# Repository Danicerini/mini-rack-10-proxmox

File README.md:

# Mini rack 10" per cluster Proxmox

Armadio da 10 pollici stampato in 3D per **tre mini PC** (un cluster Proxmox), uno **switch di rete** e una **plancia di controllo** con display. Si monta tutto con viti normali, senza colla e senza inserti a caldo.

|  |  |
|---|---|

## Cosa c'è
- **4 vani**:
  - 1 vano alto 51 mm in basso per un Teclast N30;
  - 2 vani da 1U per due HP EliteDesk Mini (G2 e G5);
  - 1 vano da 2U in alto con switch, ESP32 e plancia inclinata.
- **Frontali con display OLED** per ogni PC: nome, temperatura, CPU, RAM e da quanto è acceso. Il vetro del display arriva a filo del frontale.
- **Plancia di controllo inclinata**:
  - display TFT da 2,4" con 5 pagine (panoramica, nodi, macchine, backup e rete, impostazioni);
  - barra a 10 LED con la CPU media del cluster (lampeggia tutta se il cluster perde il quorum);
  - joystick a 4 direzioni: cambia pagina, apre nodi e macchine e, **tenendo premuto 1,5 s**, accende (Wake-on-LAN), riavvia o spegne i nodi e accende, riavvia, spegne o ferma VM e container;
  - impostazioni dal joystick (luminosità, spegnimento schermi da 5 secondi a 30 minuti, scorrimento automatico) salvate nella memoria dell'ESP32: restano anche dopo un riavvio;
  - sensore di movimento PIR, che spegne i display quando non c'è nessuno.
  - Il logo Proxmox non è incluso (è un marchio): senza il file `logo_proxmox.h` il firmware scrive "Proxmox" in testo. Puoi crearlo tu dal media kit ufficiale di Proxmox.
- **Pannelli laterali traforati** a esagoni per l'aria, **maniglie** per trasportarlo e **piedini**.
- Misure: **260 × 220 × 293 mm** circa.
- Si stampa tutto su un piatto da **256 × 256 mm** (Bambu Lab A1, P1, X1).

## Struttura della repo
| Cartella | Cosa contiene |
|---|---|
| `stl/` | Tutti i pezzi da stampare. `__x4` nel nome vuol dire che ne servono 4. `00_rack_montato_solo_da_guardare.stl` non va stampato. |
| `stampa_bambu/` | Progetto Bambu Studio (`.3mf`) con i pezzi già disposti sui piatti. |
| `openscad/` | Sorgente parametrico `rack10.scad`: tutte le misure sono in cima al file. |
| `istruzioni/` | Manuale di montaggio in PDF, passo per passo, con la viteria in scala 1:1. |
| `elettronica/firmware/` | Firmware ESP32 della plancia e due sketch di prova per i fili. |
| `elettronica/server/` | Script per Proxmox che manda lo stato del cluster all'ESP32 via USB. |
| `elettronica/pcb/` | Circuito stampato (facoltativo) che sostituisce la basetta e i fili Dupont. |
| `elettronica/Schema_collegamenti.pdf` | Schema di tutti i fili. |
| `script/` | Script Python che rigenerano il manuale e il progetto Bambu. |

## Pezzi da stampare
| N. | Pezzo | Quanti | Colore usato |
|---|---|---|---|
| 01 | Montante | 4 | Nero |
| 03 | Cornice sotto | 1 | Bianco |
| 04 | Cornice sopra | 1 | Bianco |
| 05 | Pannello laterale destro | 1 | Nero |
| 06 | Pannello laterale sinistro | 1 | Nero |
| 09 | Maniglia | 2 | Bianco |
| 10 | Piedino | 4 | Bianco |
| 11 | Ripiano HP | 2 | Nero |
| 12 | Ripiano pve1 (Teclast) | 1 | Nero |
| 13 | Ripiano plancia (switch + ESP32) | 1 | Nero |
| 14 | Frontale pve1 | 1 | Nero |
| 15 | Frontale pve2 | 1 | Nero |
| 16 | Frontale pve3 | 1 | Nero |
| 17 | Plancia inclinata | 1 | Nero |
| 18 | Barra fermo switch | 1 | Nero |

In tutto sono **24 pezzi in PLA**. I numeri 02, 07 e 08 non esistono: sono pezzi di versioni precedenti.

**Impostazioni consigliate**:
- PLA, strati da 0,2 mm, 3 pareti e riempimento al 15-20%;
- nel `.3mf` i pezzi sono già disposti e orientati sui piatti: controlla nell'anteprima se qualcuno ha bisogno di supporti;
- tieni il rack lontano da sole e fonti di calore, perché il PLA si deforma sopra i 55 °C circa.

## Viteria
| Sigla | Vite | Quante | Dove |
|---|---|---|---|
| A | M6 × 35 testa bombata | 20 | frontali e plancia (va bene anche M6 × 40) |
| B | M6 × 25 testa bombata | 8 | alette posteriori dei ripiani |
| C | Autofilettante 4 × 25 testa svasata | 8 | cornici sui montanti |
| D | Autofilettante 4 × 20 testa tonda | 4 | maniglie |
| E | Autofilettante 4 × 12 testa tonda | 4 | piedini |
| F | Autofilettante 3 × 12 testa svasata | 26 | pannelli laterali e barra dello switch |
| G | M2 × 6 testa bombata | 14 | display OLED e sensore PIR |
| H | M2,5 × 8 testa bombata | 4 | joystick |
| I | M2,5 × 4 testa bombata | 4 | display TFT |
| N | Dado M6 | 28 | nelle sedi dei montanti |
| R | Rondella piana M6 | 20 | sotto la testa delle viti A |

**Attrezzi**: cacciavite PH2, brugole da 4, 1,5 e 1,3 mm, chiave da 10 o pinza.

## Componenti
**Computer e rete** (il rack è disegnato su queste misure):
| Cosa | Note | Quanti |
|---|---|---|
| Teclast N30 | 114 × 106 × 43,5 mm | 1 |
| HP EliteDesk 800 G2 / G5 Desktop Mini | 177 × 175 × 34 mm | 2 |
| Switch TP-Link TL-SG608E | 8 porte, 158 × 100 × 25 mm | 1 |
| Cavi di rete corti | Cat 6, da 0,25 a 0,5 m | 4 |
| Cavo USB **per dati** | dall'ESP32 a un nodo Proxmox | 1 |

**Elettronica della plancia**:
| Cosa | Note | Quanti |
|---|---|---|
| ESP32 DevKit con basetta a morsetti | basetta 77 × 63 mm | 1 |
| Display TFT 2,4" ST7789 | 320 × 240, SPI | 1 |
| Display OLED 0,96" SSD1306 | I2C, indirizzo 0x3C | 3 |
| Barra LED a 10 segmenti | con due 74HC595 | 1 |
| Joystick KY-023 | 34 × 26 mm | 1 |
| Sensore di movimento HC-SR501 | con lente | 1 |
| Cavi Dupont femmina-femmina | 20 cm | circa 30 |

Con altri PC o un altro switch basta cambiare le misure in cima a `openscad/rack10.scad` e riesportare gli STL.

## Montaggio
Segui il manuale [`istruzioni/Manuale_montaggio_rack_10pollici.pdf`](istruzioni/Manuale_montaggio_rack_10pollici.pdf): ci sono 15 passi illustrati, la viteria disegnata in scala 1:1 (stampa la pagina al 100%) e i controlli finali.

> **Nota sui display OLED:** nella versione attuale dei frontali (14, 15, 16) l'OLED non va più sulle torrette, come mostrato nel manuale. Ora il circuito entra in un incavo sul retro del frontale e il vetro arriva a filo davanti, come nel TFT. Dietro c'è una scanalatura per le saldature dei pin. Le misure del vetro sono nei parametri `oled_glass*` e `oled2_*` di `rack10.scad`: controllale col calibro sui tuoi display.

## Elettronica e software
1. **Collegamenti**: segui [`elettronica/Schema_collegamenti.pdf`](elettronica/Schema_collegamenti.pdf). In breve:

   | Cosa | GPIO |
   |---|---|
   | TFT | CS 5, RESET 4, DC 16, MOSI 23, SCK 18, LED 25 |
   | OLED | SCL 22 per tutti; SDA: pve1 21, pve2 19, pve3 17 |
   | 74HC595 | DS 13, SH_CP 14, ST_CP 27, OE 15 |
   | PIR | 39 |
   | Joystick | VRx 34, VRy 35, SW 33 (alimentato a 3V3) |

2. **Firmware**: apri `elettronica/firmware/cluster_completo/cluster_completo.ino` con Arduino IDE o arduino-cli.
   - Core: esp32 3.x.
   - Librerie: LovyanGFX, ArduinoJson, Adafruit SSD1306 e Adafruit GFX.
   - Le opzioni sono in cima al file: `USE_PIR`, `USE_JOY`, `BRIGHT_TFT`, `SCREEN_OFF_MS` e così via.
   - I nomi dei nodi mostrati sugli OLED sono in `OLED_NODE`.
   ```
   arduino-cli compile --fqbn esp32:esp32:esp32:FlashFreq=40,FlashMode=dio cluster_completo
   arduino-cli upload  --fqbn esp32:esp32:esp32:FlashFreq=40,FlashMode=dio -p COM3 cluster_completo
   ```
   > **Flash a 40 MHz**: molti ESP32 economici hanno una flash Puya (ID `0x852016`) che a 80 MHz legge bene ma ignora in silenzio le scritture del firmware, e le impostazioni si perdono a ogni riavvio. A 40 MHz funziona. Il firmware ha i comandi seriali `SET_GET`, `SET_TEST <tft> <barra> <secondi>` e `FLASH_TEST` per controllarlo.
3. **Server**: l'ESP32 non usa il Wi-Fi. Riceve i dati via USB da un nodo Proxmox.
   - Copia `elettronica/server/cluster-status.py` in `/usr/local/bin/` sul nodo a cui colleghi l'ESP32.
   - Nelle impostazioni in cima al file metti i nomi e gli IP dei tuoi nodi.
   - Attiva il servizio:
     ```
     cp cluster-status.service /etc/systemd/system/
     chmod +x /usr/local/bin/cluster-status.py
     systemctl enable --now cluster-status
     ```
   - Lo script legge lo stato con `pvesh`, solo in lettura.
   - Lo pubblica anche su `http://IP-DEL-NODO:9101/status.json`.
   - Se l'ESP32 è attaccato a un PC Windows invece che al nodo, c'è `ponte_dati_pc.ps1`.
4. **Caricare il firmware senza staccare niente**: se l'ESP32 è collegato al nodo, puoi caricarlo da lì con esptool.
   ```
   systemctl stop cluster-status
   esptool --port /dev/ttyUSB0 --baud 460800 write-flash 0x10000 cluster_completo.ino.bin
   systemctl start cluster-status
   ```
   Carica solo `cluster_completo.ino.bin` a `0x10000`: così le impostazioni salvate restano. Il file `merged.bin` a `0x0` serve solo la prima volta (ESP32 nuovo), perché riscrive tutta la memoria e cancella le impostazioni.

### PCB (facoltativa)
In `elettronica/pcb/` c'è una scheda da 70 × 47 mm che sostituisce basetta e fili. Ci sono due versioni:
- **THT**, da saldare tutta a mano;
- **SMD**, con chip e resistenze montati in fabbrica.

I file per l'ordine (gerber, BOM e CPL per JLCPCB) sono in `elettronica/pcb/produzione/`. I file KiCad sono in `elettronica/pcb/kicad/`. **La scheda non è ancora stata prodotta né provata.**

## Licenza
[CC BY-NC-SA 4.0](LICENSE): puoi stamparlo, modificarlo e condividerlo citando l'autore, **non a scopo commerciale**, e con la stessa licenza.

Il modello è scaricabile anche su MakerWorld.

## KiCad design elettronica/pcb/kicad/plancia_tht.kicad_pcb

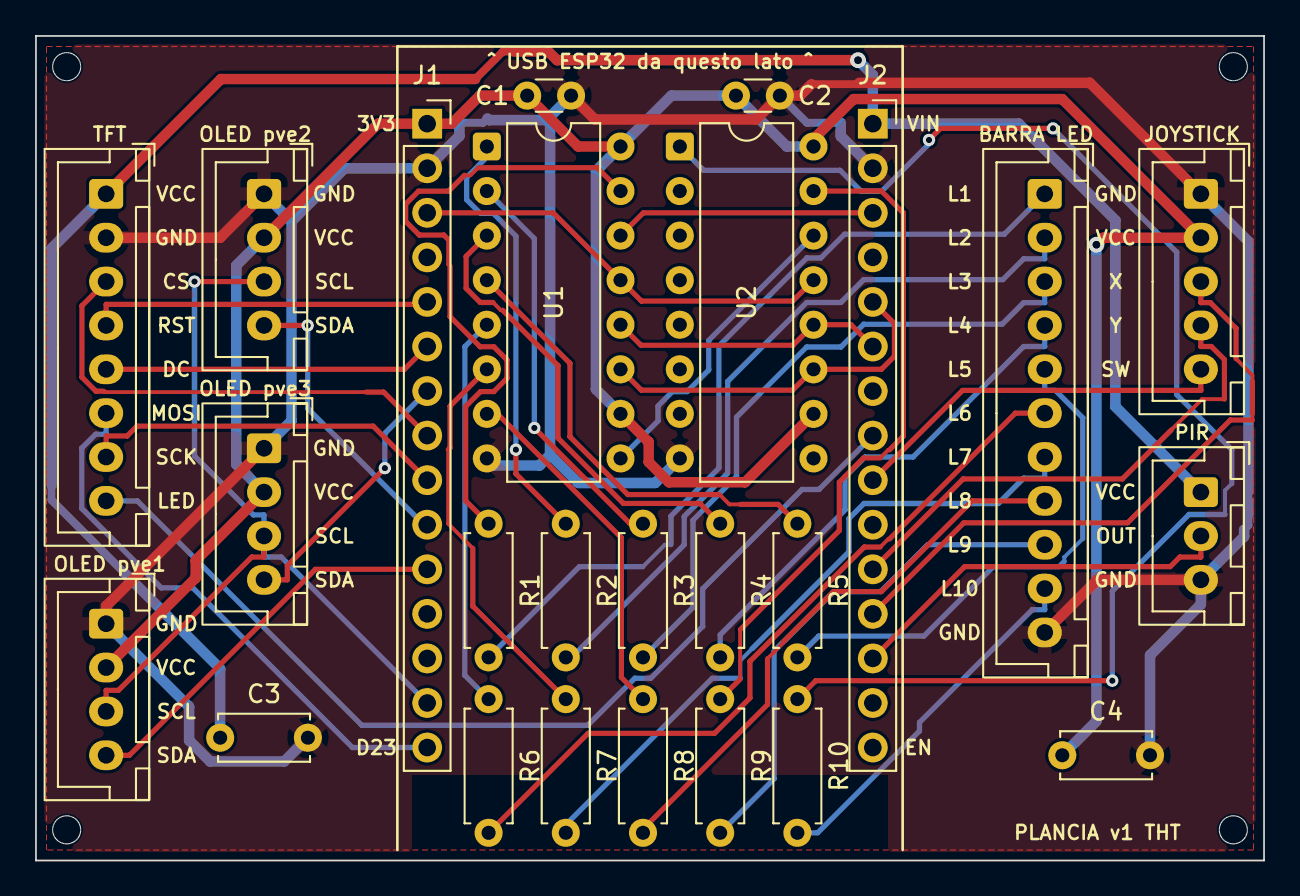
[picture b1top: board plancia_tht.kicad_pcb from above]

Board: 2 copper layers, 70.0 x 47.0 mm, 29 parts (0 on the bottom side), 42 nets.

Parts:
C1, C2: 100nF; C_Disc_D3.0mm_W1.6mm_P2.50mm
C3: 10uF 5V; C_Disc_D5.0mm_W2.5mm_P5.00mm
C4: 10uF 3V3; C_Disc_D5.0mm_W2.5mm_P5.00mm
H1, H2, H3, H4: M1.4
J1: ESP32 sx (3V3..D23); PinSocket_1x15_P2.54mm_Vertical
J2: ESP32 dx (VIN..EN); PinSocket_1x15_P2.54mm_Vertical
J3: TFT: VCC GND CS RST DC MOSI SCK LED; JST_XH_B8B-XH-A_1x08_P2.50mm_Vertical
J4: OLED pve1: GND VCC SCL SDA; JST_XH_B4B-XH-A_1x04_P2.50mm_Vertical
J5: OLED pve2: GND VCC SCL SDA; JST_XH_B4B-XH-A_1x04_P2.50mm_Vertical
J6: OLED pve3: GND VCC SCL SDA; JST_XH_B4B-XH-A_1x04_P2.50mm_Vertical
J7: Barra LED: anodi 1-10, GND; JST_XH_B11B-XH-A_1x11_P2.50mm_Vertical
J8: Joystick: GND V SW? -> GND 3V3 VRX VRY SW; JST_XH_B5B-XH-A_1x05_P2.50mm_Vertical
J9: PIR: VCC OUT GND; JST_XH_B3B-XH-A_1x03_P2.50mm_Vertical
R1, R2, R3, R4, R5, R6, R7, R8, R9, R10: 220; R_Axial_DIN0207_L6.3mm_D2.5mm_P7.62mm_Horizontal
U1, U2: 74HC595; DIP-16_W7.62mm

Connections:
+3V3: C1.1, C2.1, C4.1, J1.1, J4.2, J5.2, J6.2, J8.2, U1.10, U1.16, U2.10, U2.16
+5V: C3.1, J2.1, J3.1, J9.1
GND: C1.2, C2.2, C3.2, C4.2, J1.2, J2.2, J3.2, J4.1, J5.1, J6.1, J7.11, J8.1, J9.3, U1.8, U2.8
IO4_TFT_RST: J1.5, J3.4
IO5_TFT_CS: J1.8, J3.3
IO13_DS: J2.3, U1.14
IO14_SHCP: J2.5, U1.11, U2.11
IO15_OE: J1.3, U1.13, U2.13
IO16_TFT_DC: J1.6, J3.5
IO17_SDA3: J1.7, J6.4
IO18_SCK: J1.9, J3.7
IO19_SDA2: J1.10, J5.4
IO21_SDA1: J1.11, J4.4
IO22_SCL: J1.14, J4.3, J5.3, J6.3
IO23_MOSI: J1.15, J3.6
IO25_TFT_LED: J2.8, J3.8
IO27_STCP: J2.6, U1.12, U2.12
IO33_JOY_SW: J2.9, J8.5
IO34_JOY_X: J2.12, J8.3
IO35_JOY_Y: J2.11, J8.4
IO39_PIR: J2.13, J9.2
LED1: J7.1, R1.2
LED2: J7.2, R2.2
LED3: J7.3, R3.2
LED4: J7.4, R4.2
LED5: J7.5, R5.2
LED6: J7.6, R6.2
LED7: J7.7, R7.2
LED8: J7.8, R8.2
LED9: J7.9, R9.2
LED10: J7.10, R10.2
Q1: R1.1, U1.15
Q2: R2.1, U1.1
Q3: R3.1, U1.2
Q4: R4.1, U1.3
Q5: R5.1, U1.4
Q6: R6.1, U1.5
Q7: R7.1, U1.6
Q8: R8.1, U1.7
Q9: R9.1, U2.15
Q10: R10.1, U2.1
QH_CASCATA: U1.9, U2.14

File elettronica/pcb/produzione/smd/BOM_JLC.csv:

Comment,Designator,Footprint,LCSC Part #
100nF,"C1,C2",C_0805_2012Metric,C49678
10uF,"C3,C4",C_0805_2012Metric,C15850
220,"R1,R2,R3,R4,R5,R6,R7,R8,R9,R10",R_0805_2012Metric,C17557
74HC595D,"U1,U2",SOIC-16_3.9x9.9mm_P1.27mm,C5947

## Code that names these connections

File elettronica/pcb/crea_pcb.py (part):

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
# ---------------------------------------------------------------- 74HC595 x2 (sotto l'ESP)
def hc595(ref, x, y, ds, q):
    pins = {"16": "+3V3", "10": "+3V3", "8": "GND", "14": ds, "11": "IO14_SHCP", "12": "IO27_STCP", "13": "IO15_OE"}
    for pin, n in zip(["15", "1", "2", "3", "4", "5", "6", "7"], q): pins[pin] = n
    if ref == "U1": pins["9"] = "QH_CASCATA"
    if V == "tht":
        fp = place("Package_DIP", "DIP-16_W7.62mm", ref, "74HC595", x, y, 0, pins)
        fp.Reference().SetPosition(pcbnew.VECTOR2I(MM(x + 3.81), MM(y + 8.89))); fp.Reference().SetTextAngleDegrees(90)
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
